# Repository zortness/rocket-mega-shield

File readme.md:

Rocket Mega Shield Revision 2
=============================

These are the Eagle files for an Arduino Mega shield with sensors and features needed by aviation and rocketry enthusiasts. 
The board is also designed to be extremely easy to use for any hobbyist application. 

These files are released under the [Creative Commons Attribution-ShareAlike](http://creativecommons.org/licenses/by-sa/3.0/) license. 
You're free to use and modify them for any purpose, including commercial.

These files make use of footprints taken from the [Adafruit Eagle Library](https://github.com/adafruit/Adafruit-Eagle-Library) 
and [Sparkfun Eagle Libraries](https://github.com/sparkfun/SparkFun-Eagle-Libraries). 

My library of modified parts is [available here](https://github.com/zortness/zort-eagle-library).

Concept
--------
This shield is geared toward aviation purposes, specifically rocketry. The board itself does not dictate how it is used.
It can also be used for things like planes, boats, cars, or robotics, though this might be overkill for those purposes.

Features
--------
* Supports 5V and 3.3V boards (Mega or Due)
* Supports MicroSD cards that can operate in SPI mode
* Supports all XBee models, using UART Serial for communication
* -- User selectable XBee on UART0 or UART1 via switch
* -- Tie-down holes included in layout
* 10Hz GPS tied to UART2
* -- External GPS Antenna u.FL connector
* High Sensitivity BMP180 Altimeter (barometric pressure and temperature)
* Full 9-degrees-of-freedom capabilities
* -- 3-Axis 16G accelerometer and magnometer (LSM303DLHCTR)
* -- 3-Axis 8-gauss gyroscope (L3GD20TR)
* 3-Axis 200G accelerometer for high-force calculations (ADXL377)
* External reverse-polarity-protected power supply via JST2 connector
* -- Will also power the Arduino
* -- Can also be powered by the Arduino over USB
* -- Up to 18V
* Input voltage measuring at ~1:6 scale
* 4x high-amp MOSFETs with continuity detection
* -- Designed for rocket deployment pyrotechnics
* Automatic level-shifting for sensors (up to 5V)
* Buzzer for making loud noises
* -- MOSFET controlled, attached to PWM pin 8
* Lots of pretty flashing lights

See the [Bill of Materials](https://github.com/zortness/rocket-mega-shield/blob/master/bom.md)
and [parts manifest](https://github.com/zortness/rocket-mega-shield/blob/master/manifest.txt)
for more information.

Versions
--------
* RocketMega Revision 2.1 - Third prototype, only pin and routing changes from R2 for Due compatability
* RocketMega Revision 2 - Second prototype board, intended for wider production, August 2013
* RocketDuino Revision 1 - Initial prototype board, June 2013 

Prototype Images
----------------
Revision 2

Revision 1

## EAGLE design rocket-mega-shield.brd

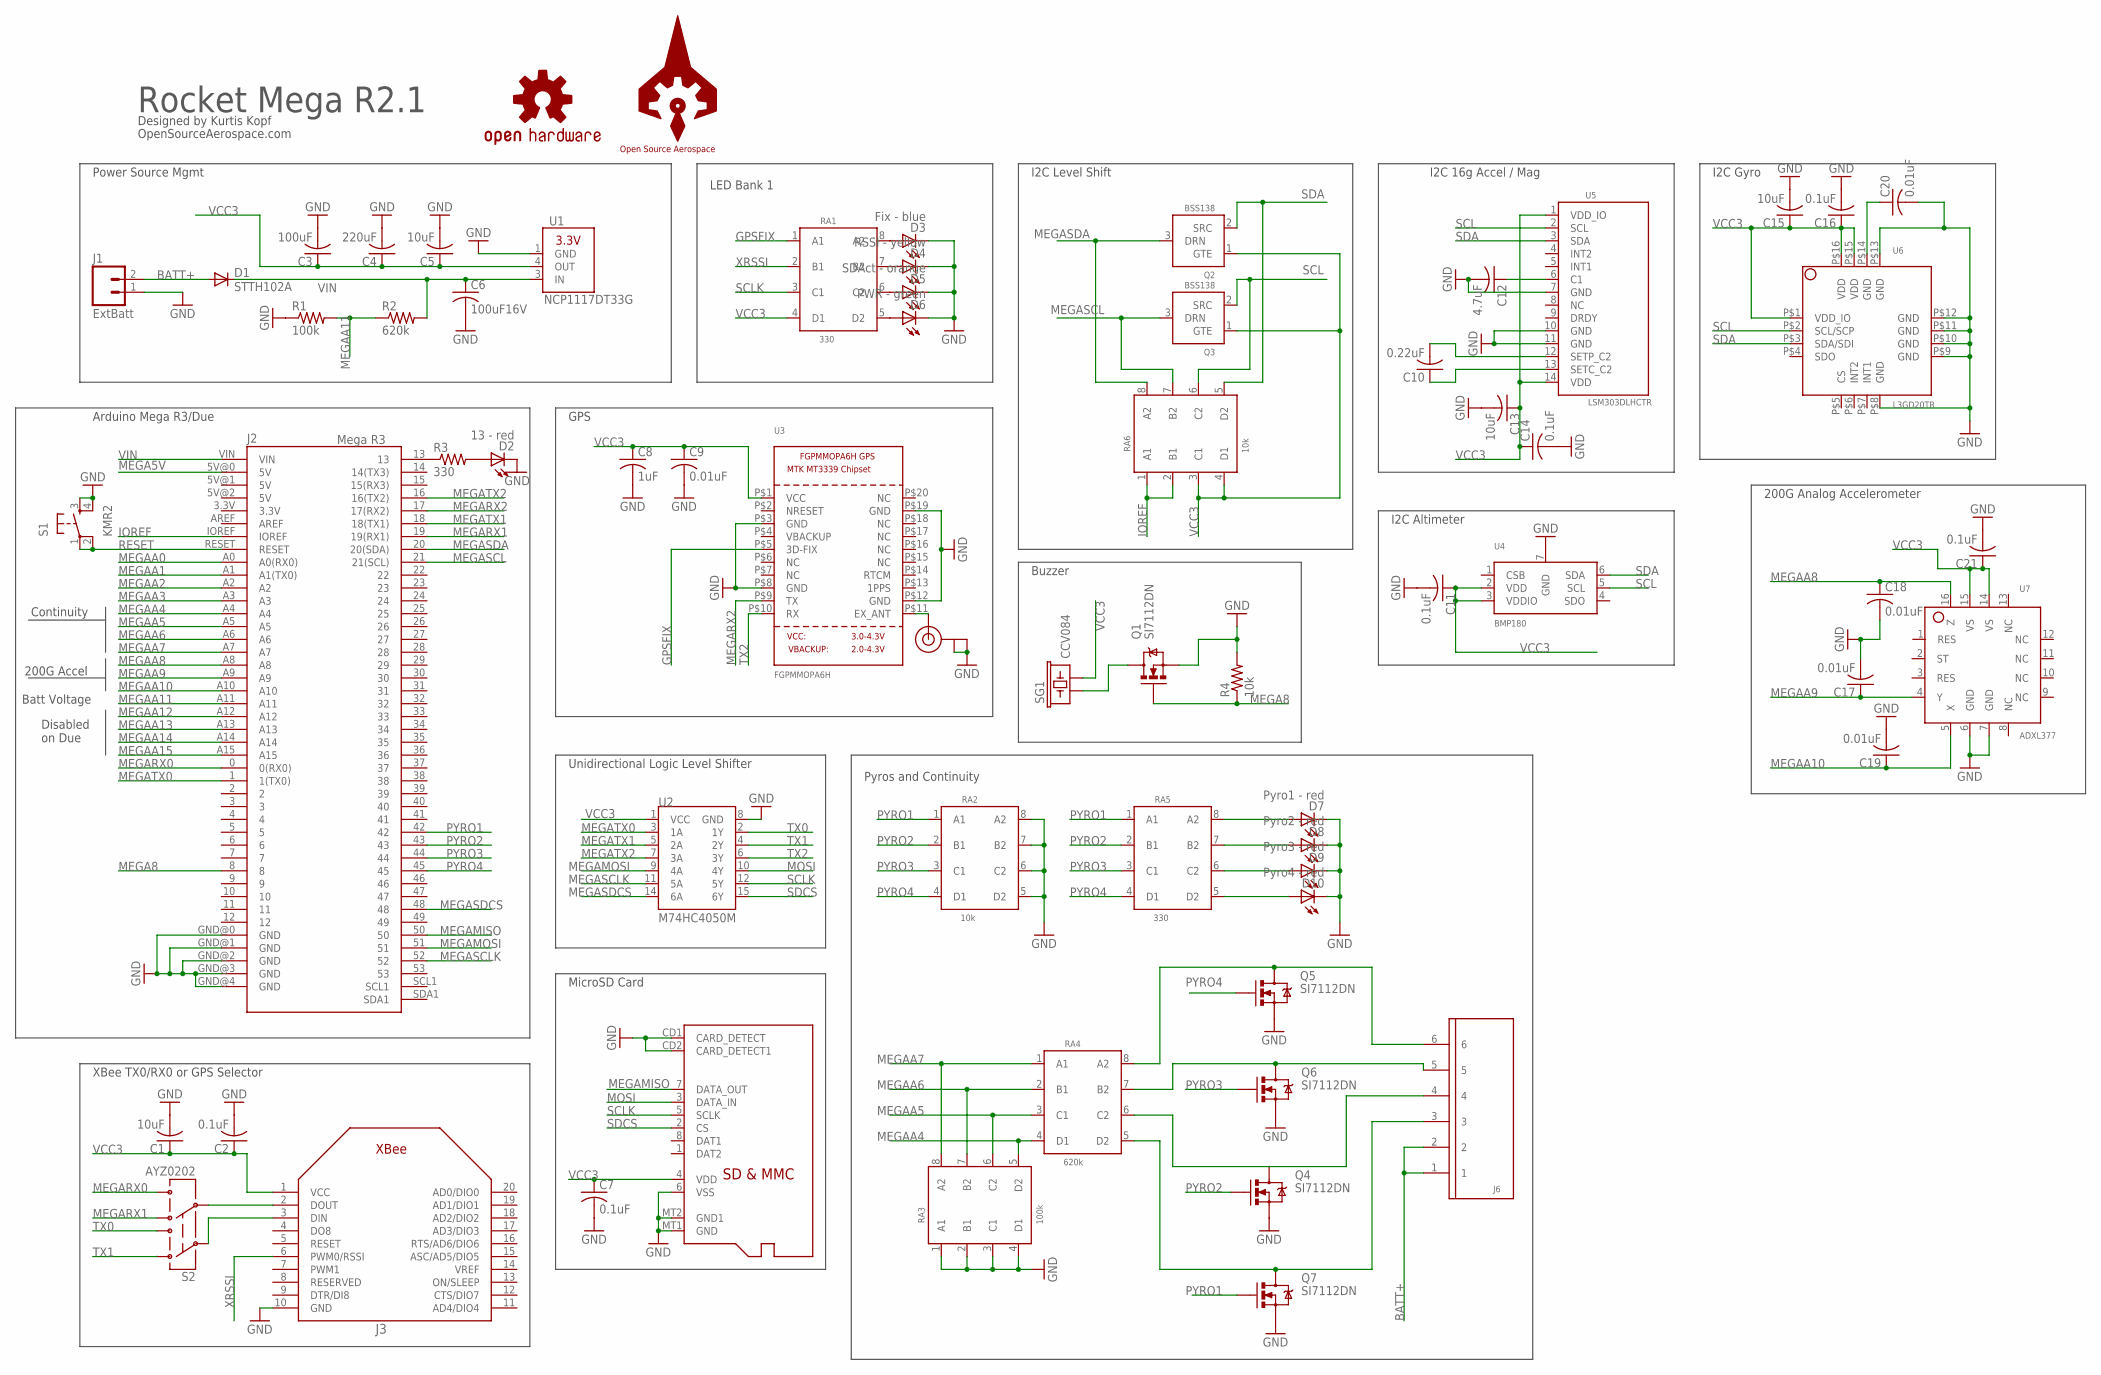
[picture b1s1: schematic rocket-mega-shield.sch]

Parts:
C1, C5, C13, C15: 10uF; C1206
C2, C7, C11, C14, C16, C21: 0.1uF; C1206
C3: 100uF; C1206
C4: 220uF; C1210
C6: 100uF16V; C1210
C8: 1uF; C1206
C9, C17, C18, C19, C20: 0.01uF; C1206
C10: 0.22uF; C1206
C12: 4.7uF; C1206
D1: STTH102A; SMA-DIODE_ALT
D2: 13 - red; LED-1206
D3: Fix - blue; LED-1206
D4: RSSI - yellow; LED-1206
D5: SDAct - orange; LED-1206
D6: PWR - green; LED-1206
D7: Pyro1 - red; LED-1206
D8: Pyro2 - red; LED-1206
D9: Pyro3 - red; LED-1206
D10: Pyro4 - red; LED-1206
J1: ExtBatt; JST-2-PTH-NS
J2: Mega R3; ARDUINO_MEGA
J3: XBEE
J4: MICROSD
J5: U.FL
J6: 1X6TERMINALBLOCK
LOGO1: OSHW-LOGOM; OSHW-LOGO-M
Q1, Q4, Q5, Q6, Q7: SI7112DN; POWERPAK1212-8
Q2, Q3: BSS138; SOT23
R1: 100k; R1206
R2: 620k; R1206
R3: 330; R1206
R4: 10k; R1206
RA1, RA5: 330; 1206X4RESISTORARRAY
RA2, RA6: 10k; 1206X4RESISTORARRAY
RA3: 100k; 1206X4RESISTORARRAY
RA4: 620k; 1206X4RESISTORARRAY
S1: KMR2; TACTILE_KMR2
S2: AYZ0202
SG1: CCV084; BUZZER-CCV
U1: NCP1117DT33G; DPAK
U2: M74HC4050M; SO016
U3: FGPMMOPA6H
U4: BMP180
U5: LSM303DLHCTR; LGA14
U6: L3GD20TR; LGA16-4X4
U7: ADXL377; LFCSP-16
U$1: OSAEROSPACEVECTOR; OSAEROSPACE_V

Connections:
BATT+: D1.A, J1.2, J6.1, J6.2
GND: C1.2, C2.2, C3.2, C4.2, C5.2, C6.2, C7.2, C8.2, C9.2, C11.2, C12.2, C13.2, C14.2, C15.2, C16.2, C17.2, C18.2, C19.2, C20.2, C21.2, D2.C, D3.C, D4.C, D5.C, D6.C, D7.C, D8.C, D9.C, D10.C, J1.1, J2.GND@0 (GND), J2.GND@1 (GND), J2.GND@2 (GND), J2.GND@3 (GND), J2.GND@4 (GND), J3.10 (GND), J4.6 (VSS), J4.CD1 (CARD_DETECT), J4.CD2 (CARD_DETECT1), J4.MT1 (GND), J4.MT2 (GND1), J5.P$1 (GND), J5.P$2 (GND), Q1.S1 (S), Q1.S2 (S), Q1.S3 (S), Q4.S1 (S), Q4.S2 (S), Q4.S3 (S), Q5.S1 (S), Q5.S2 (S), Q5.S3 (S), Q6.S1 (S), Q6.S2 (S), Q6.S3 (S), Q7.S1 (S), Q7.S2 (S), Q7.S3 (S), R1.1, R4.2, RA2.5 (D2), RA2.6 (C2), RA2.7 (B2), RA2.8 (A2), RA3.1 (A1), RA3.2 (B1), RA3.3 (C1), RA3.4 (D1), S1.3, S1.4, U1.1 (GND), U2.8 (GND), U3.P$3 (GND), U3.P$8 (GND), U3.P$12 (GND), U3.P$19 (GND), U4.7 (GND), U5.7 (GND), U5.10 (GND), U5.11 (GND), U6.P$8 (GND), U6.P$9 (GND), U6.P$10 (GND), U6.P$11 (GND), U6.P$12 (GND), U6.P$13 (GND), U7.6 (GND), U7.7 (GND)
GPSFIX: RA1.1 (A1), U3.P$5 (3D-FIX)
IOREF: J2.IOREF, RA6.1 (A1), RA6.2 (B1)
MEGA5V: J2.5V@0 (5V)
MEGA8: J2.8, Q1.G, R4.1
MEGAA0: J2.A0 (A0(RX0))
MEGAA1: J2.A1 (A1(TX0))
MEGAA2: J2.A2
MEGAA3: J2.A3
MEGAA4: J2.A4, RA3.5 (D2), RA4.4 (D1)
MEGAA5: J2.A5, RA3.6 (C2), RA4.3 (C1)
MEGAA6: J2.A6, RA3.7 (B2), RA4.2 (B1)
MEGAA7: J2.A7, RA3.8 (A2), RA4.1 (A1)
MEGAA8: C18.1, J2.A8, U7.16 (Z)
MEGAA9: C17.1, J2.A9, U7.4 (Y)
MEGAA10: C19.1, J2.A10, U7.5 (X)
MEGAA11: J2.A11, R1.2, R2.1
MEGAA12: J2.A12
MEGAA13: J2.A13
MEGAA14: J2.A14
MEGAA15: J2.A15
MEGAMISO: J2.50, J4.7 (DATA_OUT)
MEGAMOSI: J2.51, U2.9 (4A)
MEGARX0: J2.0 (0(RX0)), S2.4 (6)
MEGARX1: J2.19 (19(RX1)), S2.6 (4)
MEGARX2: J2.17 (17(RX2)), U3.P$9 (TX)
MEGASCL: J2.21 (21(SCL)), Q3.3 (DRN), RA6.7 (B2)
MEGASCLK: J2.52, U2.11 (5A)
MEGASDA: J2.20 (20(SDA)), Q2.3 (DRN), RA6.8 (A2)
MEGASDCS: J2.48, U2.14 (6A)
MEGATX0: J2.1 (1(TX0)), U2.3 (1A)
MEGATX1: J2.18 (18(TX1)), U2.5 (2A)
MEGATX2: J2.16 (16(TX2)), U2.7 (3A)
MOSI: J4.3 (DATA_IN), U2.10 (4Y)
unnamed: D6.A, RA1.5 (D2)
unnamed: D5.A, RA1.6 (C2)
unnamed: J6.3, Q7.D1 (D), Q7.D2 (D), Q7.D3 (D), Q7.D4 (D), Q7.DPAD (D), RA4.5 (D2)
unnamed: J6.4, Q4.D1 (D), Q4.D2 (D), Q4.D3 (D), Q4.D4 (D), Q4.DPAD (D), RA4.6 (C2)
unnamed: C10.2, U5.12 (SETP_C2)
unnamed: C10.1, U5.13 (SETC_C2)
unnamed: C12.1, U5.6 (C1)
unnamed: C20.1, U6.P$14 (GND)
unnamed: J2.13, R3.1
unnamed: J5.P$3 (SIGNAL), U3.P$11 (EX_ANT)
unnamed: D4.A, RA1.7 (B2)
unnamed: D3.A, RA1.8 (A2)
unnamed: Q1.D1 (D), Q1.D2 (D), Q1.D3 (D), Q1.D4 (D), Q1.DPAD (D), SG1.+ (1)
unnamed: D2.A, R3.2
unnamed: D10.A, RA5.5 (D2)
unnamed: D9.A, RA5.6 (C2)
unnamed: D8.A, RA5.7 (B2)
unnamed: D7.A, RA5.8 (A2)
unnamed: J3.2 (DOUT), S2.5
unnamed: J3.3 (DIN), S2.2
unnamed: J6.6, Q5.D1 (D), Q5.D2 (D), Q5.D3 (D), Q5.D4 (D), Q5.DPAD (D), RA4.8 (A2)
unnamed: J6.5, Q6.D1 (D), Q6.D2 (D), Q6.D3 (D), Q6.D4 (D), Q6.DPAD (D), RA4.7 (B2)
PYRO1: J2.42, Q7.G, RA2.1 (A1), RA5.1 (A1)
PYRO2: J2.43, Q4.G, RA2.2 (B1), RA5.2 (B1)
PYRO3: J2.44, Q6.G, RA2.3 (C1), RA5.3 (C1)
PYRO4: J2.45, Q5.G, RA2.4 (D1), RA5.4 (D1)
RESET: J2.RESET, S1.1, S1.2
SCL: Q3.2 (SRC), RA6.6 (C2), U4.5 (SCL), U5.2 (SCL), U6.P$2 (SCL/SCP)
SCLK: J4.5 (SCLK), RA1.3 (C1), U2.12 (5Y)
SDA: Q2.2 (SRC), RA6.5 (D2), U4.6 (SDA), U5.3 (SDA), U6.P$3 (SDA/SDI)
SDCS: J4.2 (CS), U2.15 (6Y)
TX0: S2.1 (3), U2.2 (1Y)
TX1: S2.3 (1), U2.4 (2Y)
TX2: U2.6 (3Y), U3.P$10 (RX)
VCC3: C1.1, C2.1, C3.1, C4.1, C5.1, C7.1, C8.1, C9.1, C11.1, C13.1, C14.1, C15.1, C16.1, C21.1, J3.1 (VCC), J4.4 (VDD), Q2.1 (GTE), Q3.1 (GTE), RA1.4 (D1), RA6.3 (C1), RA6.4 (D1), SG1.- (2), U1.4 (OUT), U2.1 (VCC), U3.P$1 (VCC), U4.2 (VDD), U4.3 (VDDIO), U5.1 (VDD_IO), U5.14 (VDD), U6.P$1 (VDD_IO), U6.P$15 (VDD), U6.P$16 (VDD), U7.14 (VS), U7.15 (VS)
VIN: C6.1, D1.C, J2.VIN, R2.2, U1.3 (IN)
XRSSI: J3.6 (PWM0/RSSI), RA1.2 (B1)

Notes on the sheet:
Power Source Mgmt
Arduino Mega R3/Due
I2C Level Shift
200G Analog Accelerometer
I2C Altimeter
I2C 16g Accel / Mag
I2C Gyro
GPS
Unidirectional Logic Level Shifter
XBee TX0/RX0 or GPS Selector
MicroSD Card
Pyros and Continuity
Rocket Mega R2.1
LED Bank 1
200G Accel
Continuity
Batt Voltage
Buzzer
Designed by Kurtis Kopf
OpenSourceAerospace.com
Disabled on Due

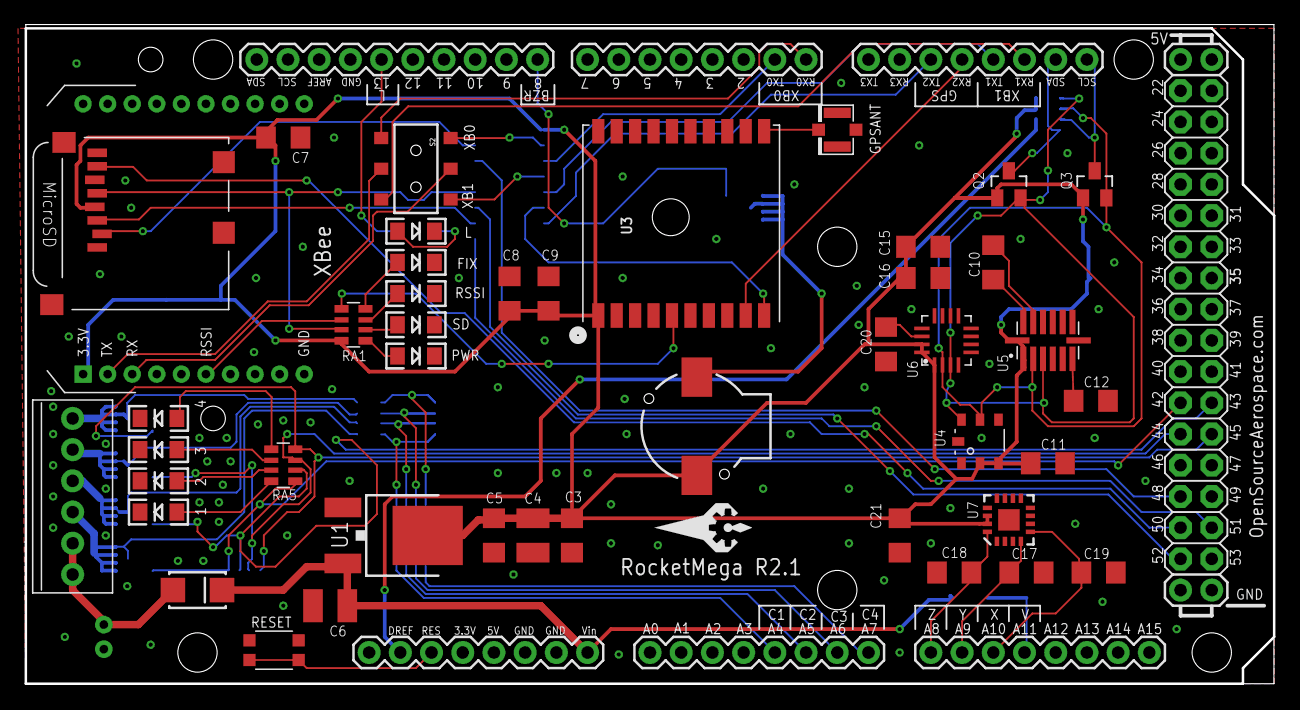
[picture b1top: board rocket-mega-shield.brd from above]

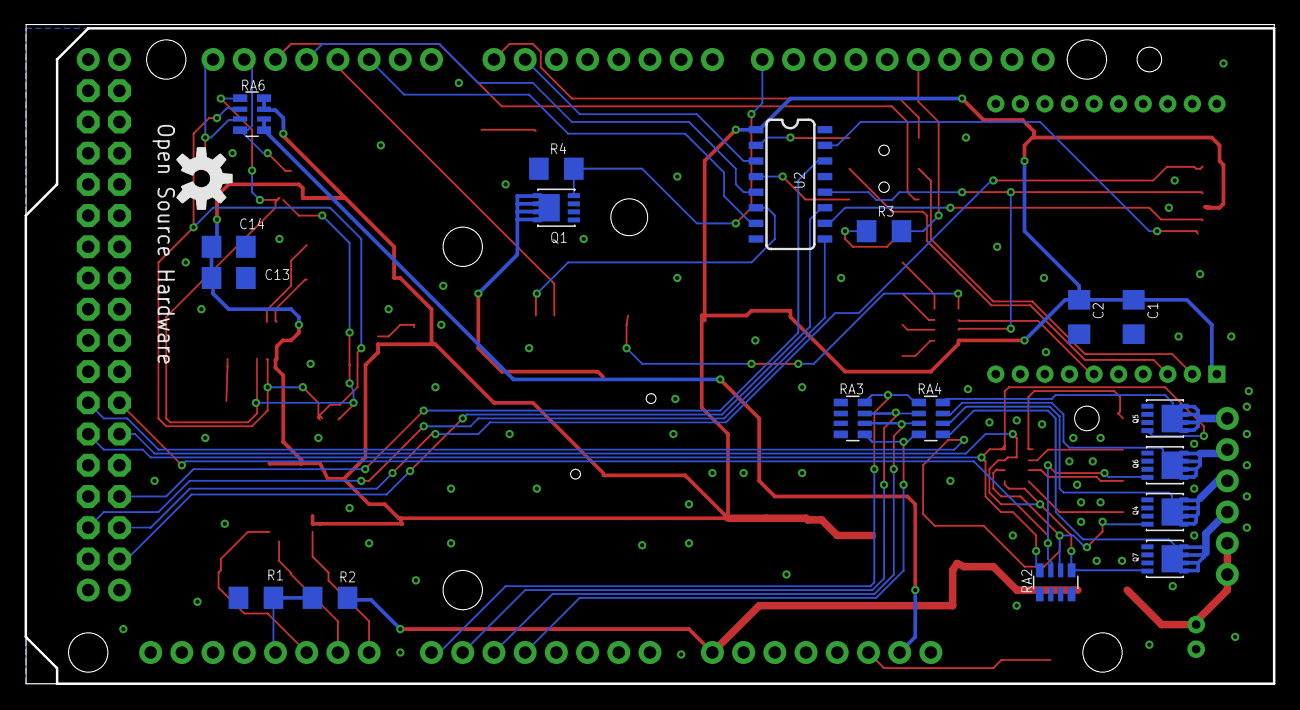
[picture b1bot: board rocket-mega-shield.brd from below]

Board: 2 copper layers, 101.6 x 53.6 mm, 66 parts (19 on the bottom side), 63 nets.

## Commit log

2013-06-20 initial commit, V1 of the board
2013-06-20 updating readme with download links
2013-06-20 adding rendered images/preview
2013-07-05 added bill of materials and costs
2013-07-20 new images added of prototype
2013-07-24 working on revision 2, not done yet
2013-07-27 initial schematic with mosfets and continuity checking
2013-07-29 working on layout for rev2
2013-07-29 updated manifest, spelled correctly this time
2013-08-01 mostly done with schematic and layout... still need to add fuse and clean up labeling
2013-08-01 fixing goofy extra via
2013-08-01 working on cleaning up the shield, will have to switch to the BMP180, went through the manifest and bill of materials
2013-08-01 fixing line breaks in BOM
2013-08-02 prettying up the BOM
2013-08-02 changed sd card, added holes to die down xb, changed reset switch, renamed all parts to match conventions, various other cleanup, adjusted BOM and manifest
2013-08-02 added buzzer on pin 8, moved all analog reads down to second set of pins, A8-A15, updated manifest, bom, and images
2013-08-02 forgot to update schematic
2013-08-02 added LED on pin 13, more cleanup, updated BOM
2013-08-02 updated readme for rev 2
2013-08-02 more readme cleanup
2013-08-03 routing and visual cleanup
2013-08-03 slight update to labelling and routing around xbee
2013-08-04 changed out mosfet on speaker for higher amperage, more cleanup
2013-08-05 changed mosfet for speaker, added osaerospace logo
2013-08-05 updated renderings
2013-08-15 changed out xbee to clean up screen printing lines, trimmed working window down to actual board size
2013-08-15 cleaning up some power nets, flipped buzzer around for better routing
2013-09-08 moving pins around to match the Due pin availablility
2013-09-16 more cleanup on the 2.1 board
2013-10-01 merging in R2.1 to master, added some images, updated readme
2013-10-01 fixing image links

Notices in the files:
parts and their libraries:
SparkFun-Connectors: Licensing: CC v3.0 Share-Alike You are welcome to use this library for commercial purposes.
